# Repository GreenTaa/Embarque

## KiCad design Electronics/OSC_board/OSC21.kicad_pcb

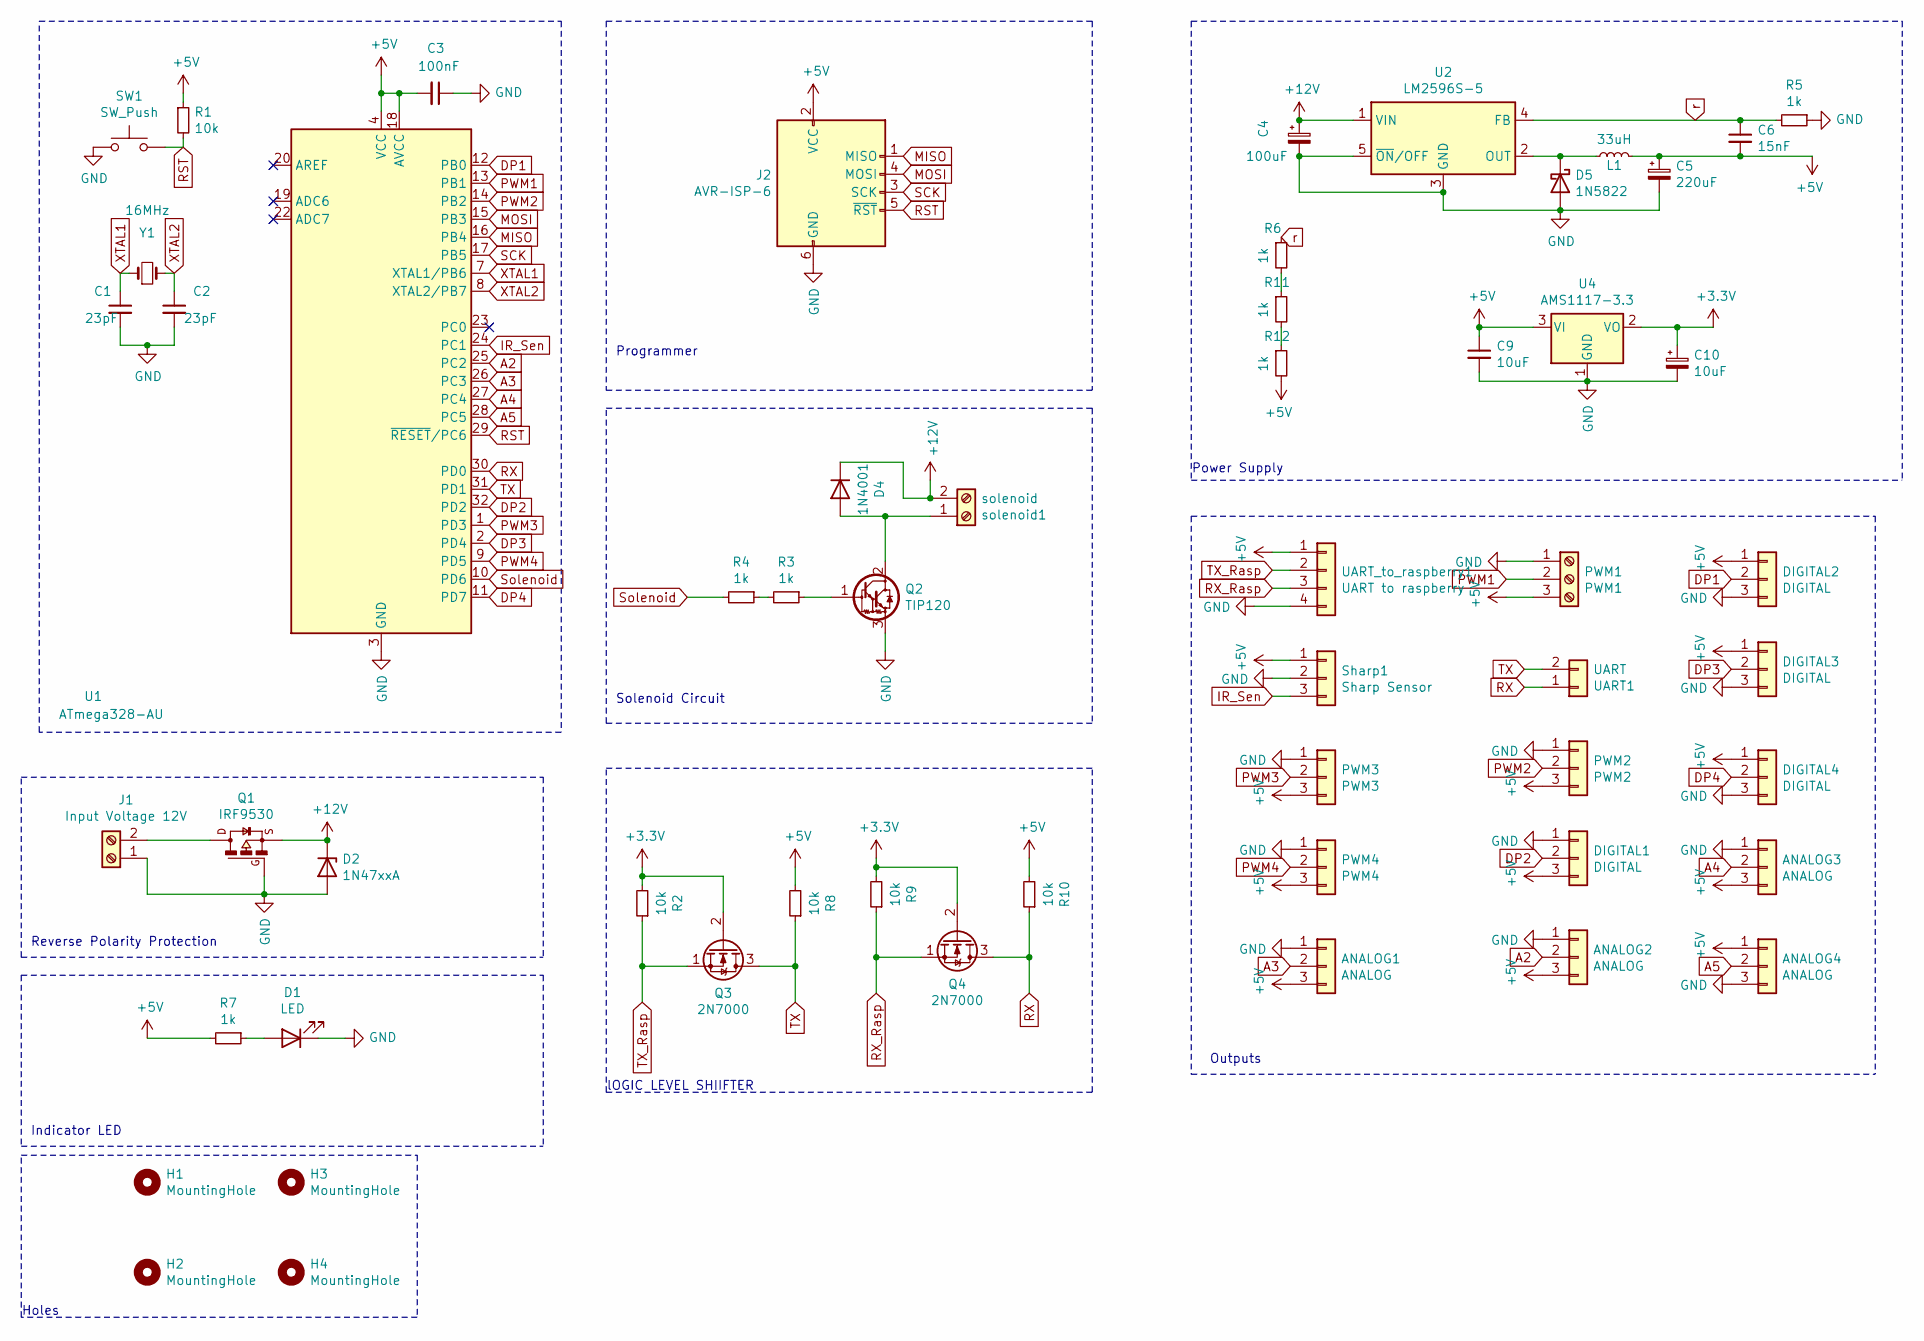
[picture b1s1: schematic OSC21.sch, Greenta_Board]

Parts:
ANALOG1, ANALOG2, ANALOG3, ANALOG4: ANALOG; JST_EH_B3B-EH-A_1x03_P2.50mm_Vertical
C1, C2: 23pF; C_Disc_D3.0mm_W2.0mm_P2.50mm
C3: 100nF; C_1206_3216Metric
C4: 100uF; CP_Elec_4x5.3
C5: 220uF; CP_Elec_4x5.3
C6: 15nF; C_Radial_D5.0mm_H5.0mm_P2.00mm
C9: 10uF; C_Radial_D5.0mm_H5.0mm_P2.00mm
C10: 10uF; CP_Elec_4x5.3
D1: LED; D_1206_3216Metric
D2: 1N47xxA; D_DO-41_SOD81_P10.16mm_Horizontal
D4: 1N4001; D_DO-41_SOD81_P10.16mm_Horizontal
D5: 1N5822; D_DO-201AD_P15.24mm_Horizontal
DIGITAL1, DIGITAL2, DIGITAL3, DIGITAL4: DIGITAL; JST_EH_B3B-EH-A_1x03_P2.50mm_Vertical
H1, H2, H3, H4: MountingHole; MountingHole_2.5mm_Pad
J1: Input Voltage 12V; TerminalBlock_Phoenix_MKDS-1,5-2_1x02_P5.00mm_Horizontal
J2: AVR-ISP-6; PinHeader_2x03_P2.00mm_Vertical
L1: 33uH; L_Radial_D6.0mm_P4.00mm
PWM1: PWM1; JST_EH_B3B-EH-A_1x03_P2.50mm_Vertical
PWM2: PWM2; TerminalBlock_Phoenix_MKDS-1,5-3-5.08_1x03_P5.08mm_Horizont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
PWM3: PWM3; JST_EH_B3B-EH-A_1x03_P2.50mm_Vertical
PWM4: PWM4; JST_EH_B3B-EH-A_1x03_P2.50mm_Vertical
Q1: IRF9530; TO-220-3_Vertical
Q2: TIP120; TO-220-3_Vertical
Q3, Q4: 2N7000; TO-92_Inline
R1, R2, R8, R9, R10: 10k; R_1206_3216Metric
R3, R4, R5, R6, R7, R11, R12: 1k; R_1206_3216Metric
SW1: SW_Push; SW_PUSH_6mm
Sharp1: Sharp Sensor; JST_EH_B3B-EH-A_1x03_P2.50mm_Vertical
U1: ATmega328-AU; TQFP-32_7x7mm_P0.8mm
U2: LM2596S-5; TO-263-5_TabPin3
U4: AMS1117-3.3; SOT-223-3_TabPin2
UART1: UART; JST_EH_B2B-EH-A_1x02_P2.50mm_Vertical
UART_to_raspberry1: UART to raspberry; JST_EH_S4B-EH_1x04_P2.50mm_Horizontal
Y1: 16MHz; Crystal_HC49-4H_Vertical
solenoid1: solenoid; TerminalBlock_Phoenix_MKDS-1,5-2_1x02_P5.00mm_Horizontal

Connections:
+3V3: C10.1, Q3.2 (G), Q4.2 (G), R2.2, R9.2, U4.2 (VO)
+5V: ANALOG1.3, ANALOG2.3, ANALOG3.3, ANALOG4.1, C3.2, C5.1, C6.2, C9.1, DIGITAL1.3, DIGITAL2.1, DIGITAL3.1, DIGITAL4.1, J2.2 (VCC), L1.2, PWM1.3, PWM2.3, PWM3.3, PWM4.3, R1.1, R7.2, R8.2, R10.2, R12.2, Sharp1.1, U1.4 (VCC), U1.6 (VCC), U1.18 (AVCC), U4.3 (VI), UART_to_raspberry1.1
+12V: C4.1, D2.1 (K), D4.1 (K), Q1.3, U2.1 (VIN), solenoid1.2
A2: ANALOG2.2, U1.25 (PC2)
A3: ANALOG1.2, U1.26 (PC3)
A4: ANALOG3.2, U1.27 (PC4)
A5: ANALOG4.2, U1.28 (PC5)
DP1: DIGITAL2.2, U1.12 (PB0)
DP2: DIGITAL1.2, U1.32 (PD2)
DP3: DIGITAL3.2, U1.2 (PD4)
DP4: DIGITAL4.2, U1.11 (PD7)
GND: ANALOG1.1, ANALOG2.1, ANALOG3.1, ANALOG4.3, C1.2, C2.2, C3.1, C4.2, C5.2, C9.2, C10.2, D1.1 (K), D2.2 (A), D5.2 (A), DIGITAL1.1, DIGITAL2.3, DIGITAL3.3, DIGITAL4.3, J1.1, J2.6 (GND), PWM1.1, PWM2.1, PWM3.1, PWM4.1, Q1.1, Q2.3 (E), R5.1, SW1.1, Sharp1.2, U1.3 (GND), U1.5 (GND), U1.21 (GND), U2.3 (GND), U2.5 (~ON~/OFF), U4.1 (GND), UART_to_raspberry1.4
IR_Sen: Sharp1.3, U1.24 (PC1)
MISO: J2.1 (MISO), U1.16 (PB4)
MOSI: J2.4 (MOSI), U1.15 (PB3)
unnamed: D1.2 (A), R7.1
unnamed: D4.2 (A), Q2.2 (C), solenoid1.1
unnamed: D5.1 (K), L1.1, U2.2 (OUT)
unnamed: J1.2, Q1.2
unnamed: Q2.1 (B), R3.1
unnamed: R3.2, R4.1
unnamed: R6.2, R11.1
unnamed: R11.2, R12.1
PWM1: PWM1.2, U1.13 (PB1)
PWM2: PWM2.2, U1.14 (PB2)
PWM3: PWM3.2, U1.1 (PD3)
PWM4: PWM4.2, U1.9 (PD5)
RST: J2.5 (~RST), R1.2, SW1.2, U1.29 (~RESET~/PC6)
RX: Q4.3 (D), R10.1, U1.30 (PD0), UART1.1
RX_Rasp: Q4.1 (S), R9.1, UART_to_raspberry1.3
SCK: J2.3 (SCK), U1.17 (PB5)
Solenoid: R4.2, U1.10 (PD6)
TX: Q3.3 (D), R8.1, U1.31 (PD1), UART1.2
TX_Rasp: Q3.1 (S), R2.1, UART_to_raspberry1.2
XTAL1: C1.1, U1.7 (XTAL1/PB6), Y1.1
XTAL2: C2.1, U1.8 (XTAL2/PB7), Y1.2
r: C6.1, R5.2, R6.1, U2.4 (FB)

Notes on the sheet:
Power Supply
Reverse Polarity Protection
Indicator LED
Programmer
Solenoid Circuit
Outputs
Holes
lOGIC LEVEL SHIIFTER

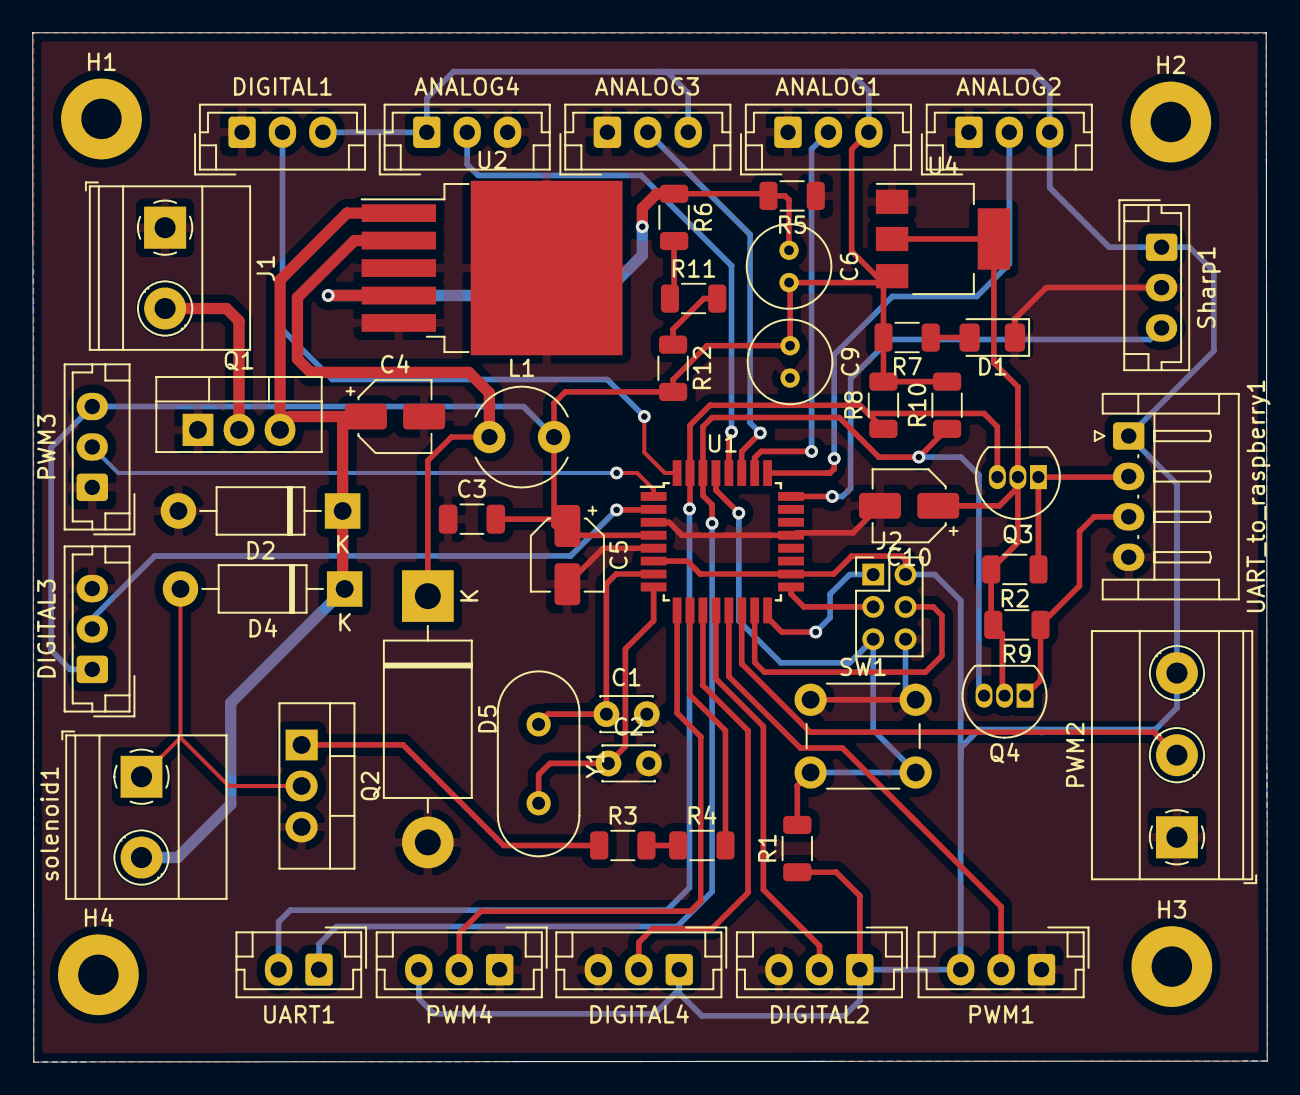
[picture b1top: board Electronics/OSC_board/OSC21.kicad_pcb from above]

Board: 2 copper layers, 76.4 x 63.7 mm, 56 parts (0 on the bottom side), 37 nets.

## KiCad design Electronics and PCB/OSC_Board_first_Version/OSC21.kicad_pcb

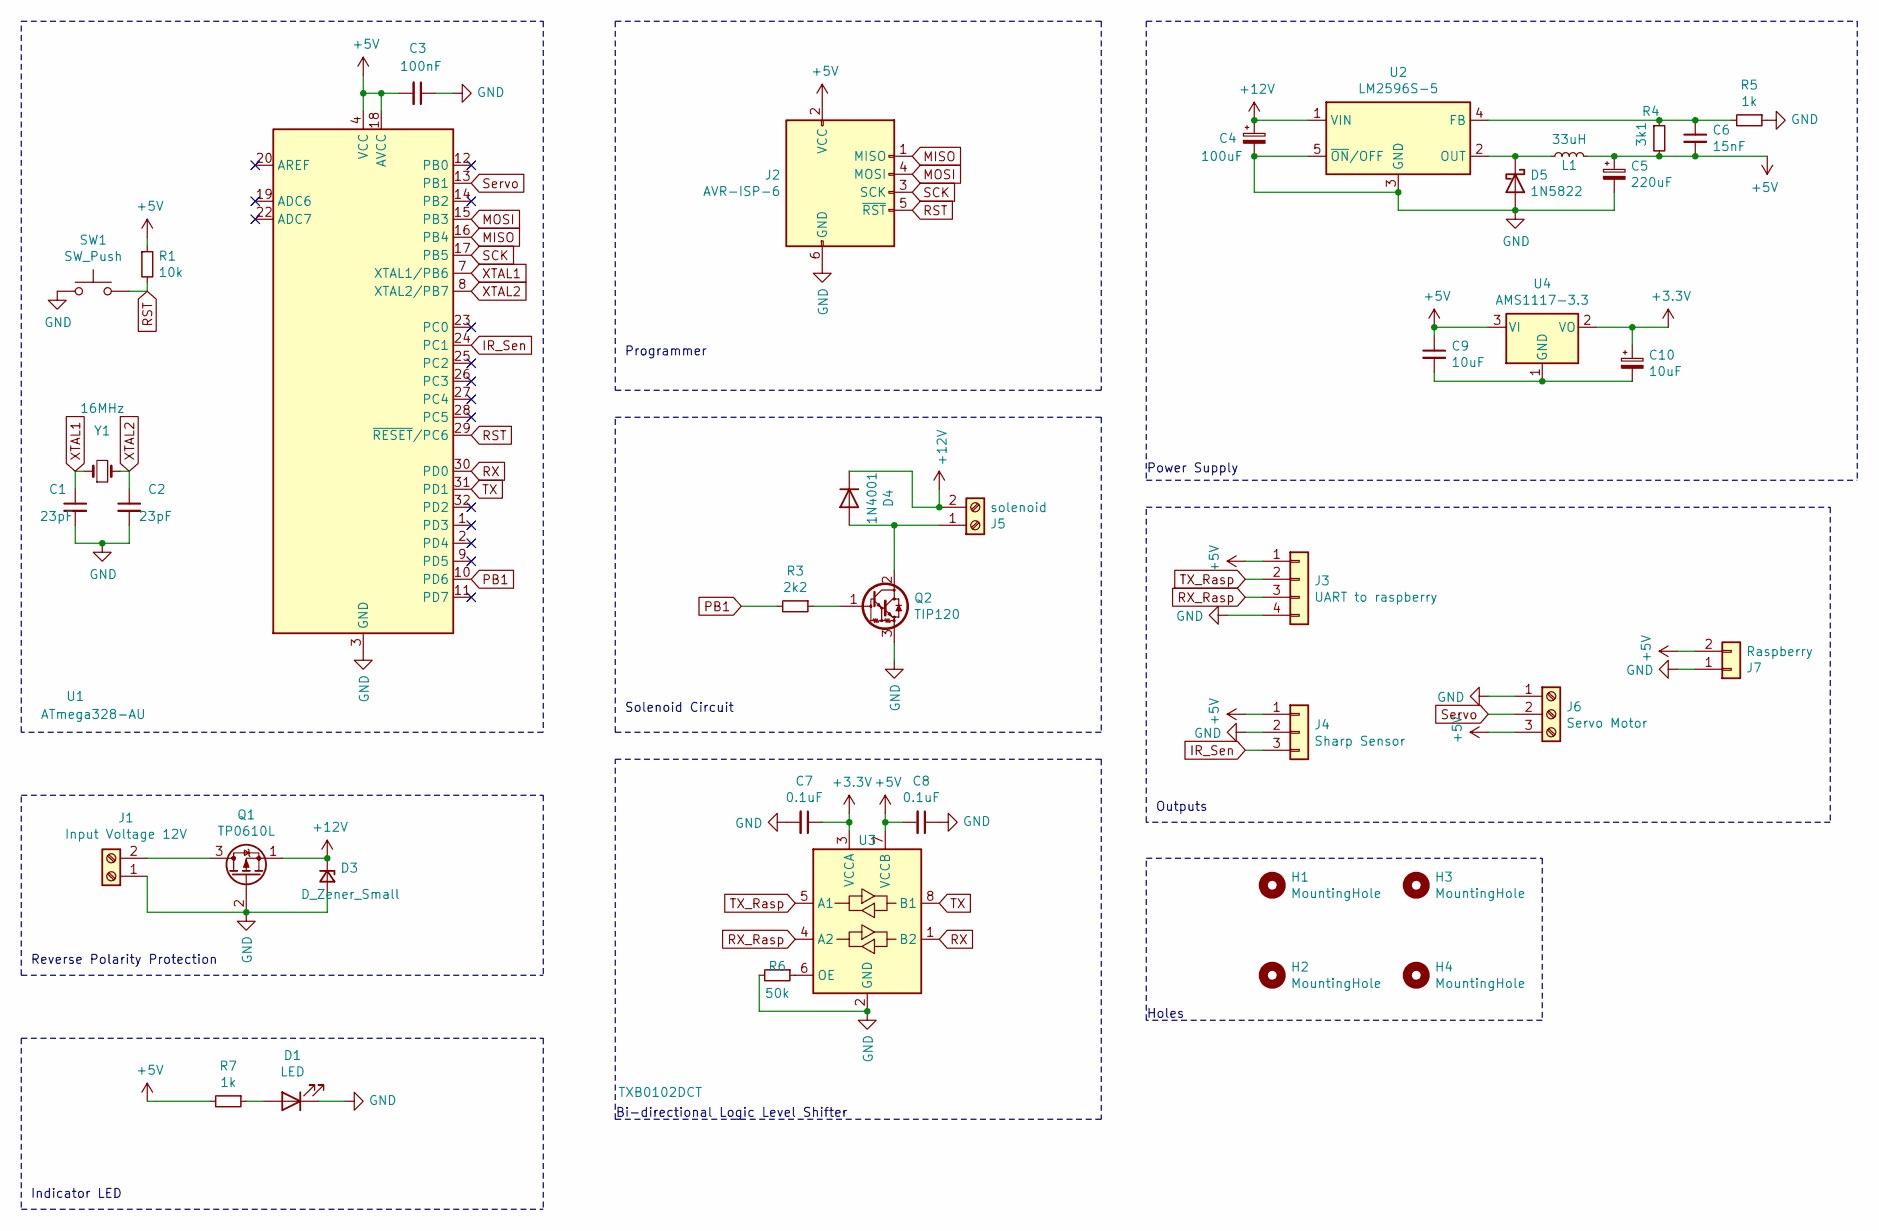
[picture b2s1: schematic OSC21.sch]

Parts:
C1, C2: 23pF; C_0603_1608Metric
C3: 100nF; C_0603_1608Metric
C4: 100uF; CP_Elec_4x3
C5: 220uF; CP_Elec_4x3
C6: 15nF; C_0603_1608Metric
C7, C8: 0.1uF; C_0603_1608Metric
C9: 10uF; C_0603_1608Metric
C10: 10uF; CP_Elec_4x3
D1: LED; D_PowerDI-123
D3: D_Zener_Small; D_SOD-123
D4: 1N4001; D_SOD-123
D5: 1N5822; D_SOD-123
H1, H2, H3, H4: MountingHole; MountingHole_2.5mm_Pad
J1: Input Voltage 12V; Altech_AK300_1x02_P5.00mm_45-Degree
J2: AVR-ISP-6; PinHeader_2x03_P2.00mm_Vertical
J3: UART to raspberry; JST_EH_S4B-EH_1x04_P2.50mm_Horizontal
J4: Sharp Sensor; JST_EH_B3B-EH-A_1x03_P2.50mm_Vertical
J5: solenoid; TerminalBlock_Phoenix_MKDS-1,5-2_1x02_P5.00mm_Horizontal
J6: Servo Motor; TerminalBlock_Phoenix_MKDS-1,5-3-5.08_1x03_P5.08mm_Horizont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
J7: Raspberry; JST_EH_B2B-EH-A_1x02_P2.50mm_Vertical
L1: 33uH; L_2010_5025Metric
Q1: TP0610L; SOT-89-3
Q2: TIP120; TO-263-2
R1: 10k; R_1206_3216Metric
R3: 2k2; R_1206_3216Metric
R4: 3k1; R_1206_3216Metric
R5, R7: 1k; R_1206_3216Metric
R6: 50k; R_1206_3216Metric
SW1: SW_Push; SW_PUSH_6mm
U1: ATmega328-AU; TQFP-32_7x7mm_P0.8mm
U2: LM2596S-5; TO-263-5_TabPin3
U3: TXB0102DCT; TSSOP-8_3x3mm_P0.65mm
U4: AMS1117-3.3; SOT-223-3_TabPin2
Y1: 16MHz; Crystal_HC49-4H_Vertical

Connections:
+3V3: C7.1, C10.1, U3.3 (VCCA), U4.2 (VO)
+5V: C3.2, C5.1, C6.2, C8.2, C9.1, J2.2 (VCC), J3.1, J4.1, J6.3, J7.2, L1.2, R1.1, R4.2, R7.2, U1.4 (VCC), U1.6 (VCC), U1.18 (AVCC), U3.7 (VCCB), U4.3 (VI)
+12V: C4.1, D3.1 (K), D4.1 (K), J5.2, Q1.1 (S), U2.1 (VIN)
GND: C1.2, C2.2, C3.1, C4.2, C5.2, C7.2, C8.1, D1.1 (K), D3.2 (A), D5.2 (A), J1.1, J2.6 (GND), J3.4, J4.2, J6.1, J7.1, Q1.2 (G), Q2.3 (E), R5.1, R6.2, SW1.1, U1.3 (GND), U1.5 (GND), U1.21 (GND), U2.3 (GND), U2.5 (~ON~/OFF), U3.2 (GND)
IR_Sen: J4.3, U1.24 (PC1)
MISO: J2.1 (MISO), U1.16 (PB4)
MOSI: J2.4 (MOSI), U1.15 (PB3)
unnamed: C6.1, R4.1, R5.2, U2.4 (FB)
unnamed: C9.2, C10.2, U4.1 (GND)
unnamed: D1.2 (A), R7.1
unnamed: D4.2 (A), J5.1, Q2.2 (C)
unnamed: D5.1 (K), L1.1, U2.2 (OUT)
unnamed: J1.2, Q1.3 (D)
unnamed: Q2.1 (B), R3.1
unnamed: R6.1, U3.6 (OE)
PB1: R3.2, U1.10 (PD6)
RST: J2.5 (~RST), R1.2, SW1.2, U1.29 (~RESET~/PC6)
RX: U1.30 (PD0), U3.1 (B2)
RX_Rasp: J3.3, U3.4 (A2)
SCK: J2.3 (SCK), U1.17 (PB5)
Servo: J6.2, U1.13 (PB1)
TX: U1.31 (PD1), U3.8 (B1)
TX_Rasp: J3.2, U3.5 (A1)
XTAL1: C1.1, U1.7 (XTAL1/PB6), Y1.1
XTAL2: C2.1, U1.8 (XTAL2/PB7), Y1.2

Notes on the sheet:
Power Supply
Reverse Polarity Protection
Indicator LED
Programmer
Solenoid Circuit
Outputs
Bi-directional Logic Level Shifter
Holes

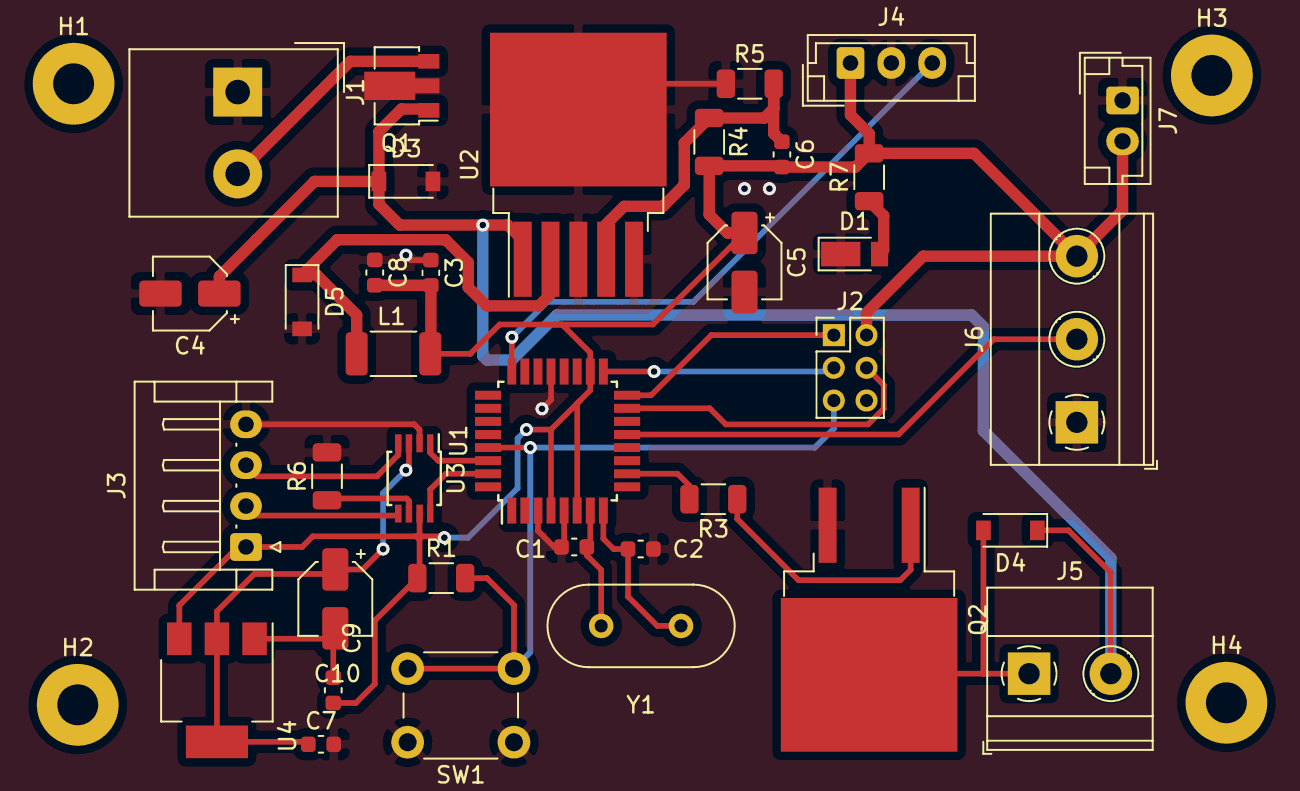
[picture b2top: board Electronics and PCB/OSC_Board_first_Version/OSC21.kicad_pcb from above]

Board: 2 copper layers, 40 parts (0 on the bottom side), 25 nets.

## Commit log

2021-09-01 add product image
2021-09-01 add user data
2021-09-01 add mechanical design
2021-09-02 Add final prototype and Real Model
2021-09-02 Add package Testing scripts
2021-09-02 Delete
2021-09-02 Add PCB Prototype
2021-09-03 Add Schematics,Bom with no root
2021-09-05 Update schematic
2021-09-06 Add System Architecture
2021-09-08 Add Tested and verified scripts
2021-09-09 Update Scripts and add Finals scripts
2021-09-09 Add model
2021-09-09 Update File
2021-09-09 Update OSC Board_ Final version Rooted
2021-09-11 Update Script
2021-09-11 Update Scripts
2021-09-11 Update Diagram
2021-09-13 Update scripts and Add servo version script
2021-09-24 Update Arduino Scripts
2021-10-08 Add Tested Script
2021-10-12 Add Demo Scripts
2021-10-15 Add Final scripts
